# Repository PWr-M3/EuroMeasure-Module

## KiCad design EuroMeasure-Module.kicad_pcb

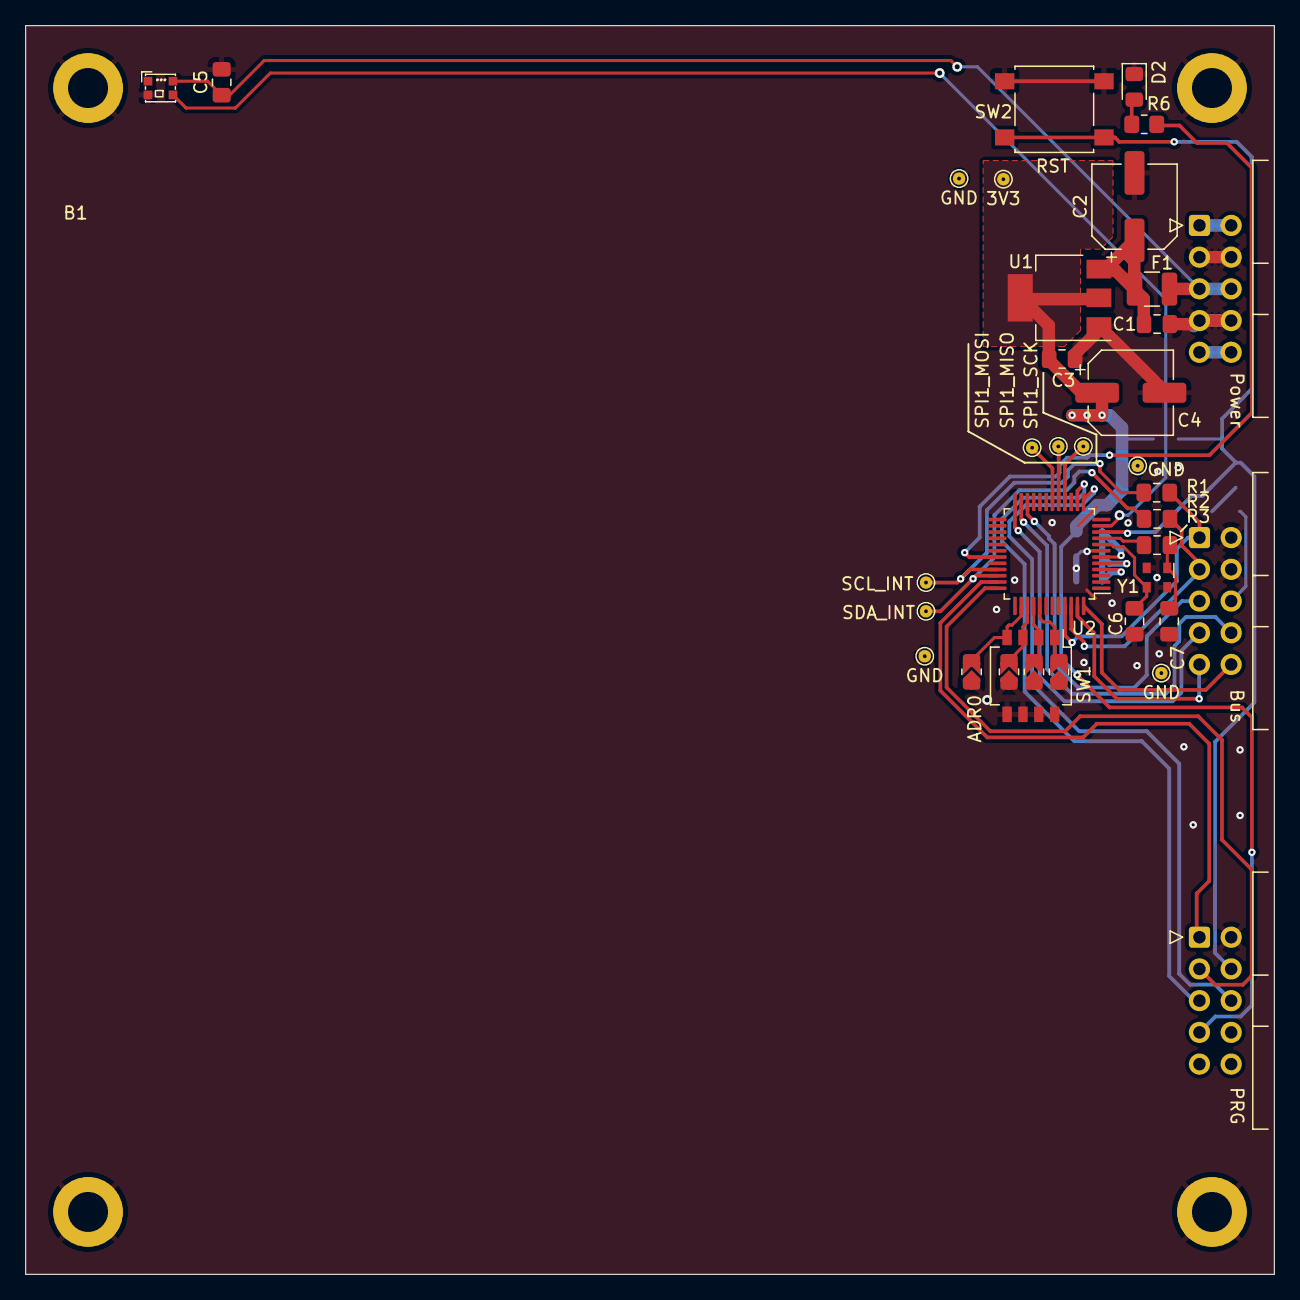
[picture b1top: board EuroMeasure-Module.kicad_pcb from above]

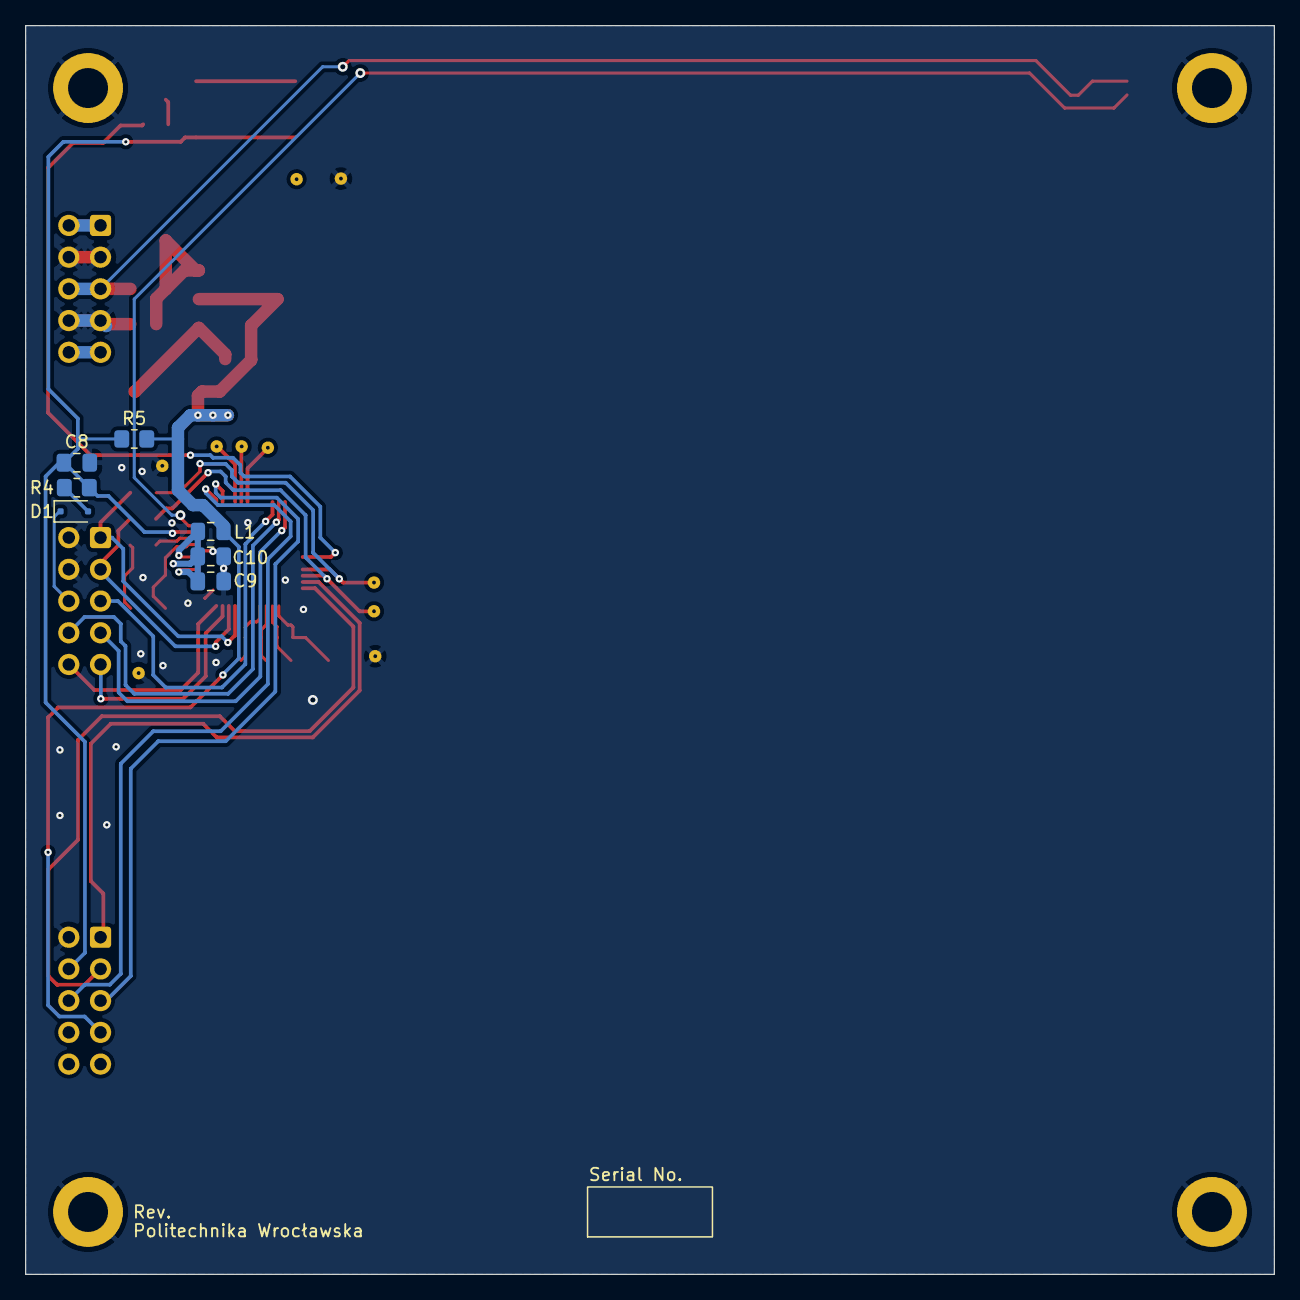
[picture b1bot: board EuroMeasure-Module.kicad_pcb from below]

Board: 2 copper layers, 100.0 x 100.0 mm, 40 parts (7 on the bottom side), 36 nets.

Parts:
B1: EuroBoard; EuroMeasureLED
C1, C3, C5, C10: 10u; C_0805_2012Metric_Pad1.18x1.45mm_HandSolder
C2, C4: 220u; CP_Elec_6.3x7.7
C6, C7: 8p; C_0805_2012Metric_Pad1.18x1.45mm_HandSolder
C8, C9: 100n; C_0805_2012Metric_Pad1.18x1.45mm_HandSolder
D1: 1N4148; D_SOD-323F
D2: RED; LED_0805_2012Metric_Pad1.15x1.40mm_HandSolder
F1: Polyfuse 0.5A; Fuse_1210_3225Metric
JP1: ADR0; R_0805_2012Metric_Jumper
JP2: ADR1; R_0805_2012Metric_Jumper
JP3: ADR2; R_0805_2012Metric_Jumper
JP4: ADR3; R_0805_2012Metric_Jumper
L1: Ferrite; L_0805_2012Metric_Pad1.15x1.40mm_HandSolder
R1, R2, R3: 0R; C_0805_2012Metric_Pad1.18x1.45mm_HandSolder
R4, R5, R6: 1k; R_0805_2012Metric_Pad1.20x1.40mm_HandSolder
SW1: SW_DIP_x04; SW_DIP_SPSTx04_Slide_Omron_A6H-4101_W6.15mm_P1.27mm
SW2: RST; SW_SPST_B3S-1000
TP1: SPI1_SCK; TestPoint_Pad_D1.0mm
TP2: SPI1_MISO; TestPoint_Pad_D1.0mm
TP3: SPI1_MOSI; TestPoint_Pad_D1.0mm
TP4: SCL_INT; TestPoint_Pad_D1.0mm
TP5: SDA_INT; TestPoint_Pad_D1.0mm
TP6, TP7, TP8, TP9: GND; TestPoint_Pad_D1.0mm
TP10: 3V3; TestPoint_Pad_D1.0mm
U1: AZ1117-3V3; SOT-223-3_TabPin2
U2: STM32G030CxT; LQFP-48_7x7mm_P0.5mm
Y1: 16MHz; Oscillator_SMD_Abracon_ASDMB-4Pin_2.5x2.0mm

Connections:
5V_INPUT: B1.5 (5V), B1.6 (5V), B1.D4 (VCC), C5.1, F1.1
15V_INPUT: B1.9 (15V), B1.10 (15V)
+3.3V: B1.27 (3.3V), C3.1, C4.1, L1.1, R5.2, TP10.1, U1.2 (VO)
-15V_INPUT: B1.1 (-15V), B1.2 (-15V)
/EuroMeasure/ADR0: JP1.1, SW1.4, U2.38 (PD0)
/EuroMeasure/ADR1: JP2.1, SW1.3, U2.39 (PD1)
/EuroMeasure/ADR2: JP3.1, SW1.2, U2.40 (PD2)
/EuroMeasure/ADR3: JP4.1, SW1.1, U2.41 (PD3)
/EuroMeasure/GP0: B1.17 (GP0), U2.24 (PB12)
/EuroMeasure/GP1: B1.18 (GP1), U2.23 (PB11)
/EuroMeasure/LED: R6.2, U2.31 (PC7)
/EuroMeasure/MCU_PWR: C9.1, C10.1, L1.2, U2.4 (VBAT), U2.5 (VREF+), U2.6 (VDD/VDDA)
/EuroMeasure/OSC_IN: R3.2, U2.9 (PF1-OSC_OUT)
/EuroMeasure/OSC_OUT: C6.1, U2.8 (PF0-OSC_IN), Y1.3
/EuroMeasure/RDY: B1.20 (RDY), U2.48 (PB9)
/EuroMeasure/RGB_LED: B1.D3 (DI), U2.11 (PA0)
/EuroMeasure/RST: B1.16 (RST), D1.1 (K)
/EuroMeasure/RST_LOCAL: B1.24 (RST), C8.1, R4.1, R5.1, SW2.2, U2.10 (NRST)
/EuroMeasure/RX_DEBUG: B1.25 (RX), U2.14 (PA3)
/EuroMeasure/SCL_EXT: B1.11 (SCL), R1.1, U2.45 (PB6)
/EuroMeasure/SCL_INT: R1.2, TP4.1, U2.33 (PA11)
/EuroMeasure/SDA_EXT: B1.13 (SDA), R2.2, U2.46 (PB7)
/EuroMeasure/SDA_INT: R2.1, TP5.1, U2.34 (PA12)
/EuroMeasure/SPI1_MISO: TP2.1, U2.17 (PA6)
/EuroMeasure/SPI1_MOSI: TP3.1, U2.18 (PA7)
/EuroMeasure/SPI1_SCK: TP1.1, U2.16 (PA5)
/EuroMeasure/SWCLK: B1.23 (SWCLK), U2.36 (PA14)
/EuroMeasure/SWDIO: B1.21 (SWDIO), U2.35 (PA13)
/EuroMeasure/TRG: B1.19 (TRG), U2.47 (PB8)
/EuroMeasure/TX_DEBUG: B1.26 (TX), U2.13 (PA2)
/EuroMeasure/~LOCKOUT: B1.15 (~LOCKOUT), U2.22 (PB10)
GND: B1.3 (GND), B1.4 (GND), B1.7 (GND), B1.8 (GND), B1.12 (GND), B1.14 (GND), B1.22 (GND), B1.D2 (GND), C1.2, C2.2, C3.2, C4.2, C5.2, C6.2, C7.2, C8.2, C9.2, C10.2, D2.1 (K), JP1.2, JP2.2, JP3.2, JP4.2, SW1.5, SW1.6, SW1.7, SW1.8, SW2.1, TP6.1, TP7.1, TP8.1, TP9.1, U1.1 (GND), U2.7 (VSS/VSSA), Y1.2, Y1.4
unnamed: C7.1, R3.1, Y1.1
unnamed: D1.2 (A), R4.2
unnamed: D2.2 (A), R6.1
unnamed: C1.1, C2.1, F1.2, U1.3 (VI)

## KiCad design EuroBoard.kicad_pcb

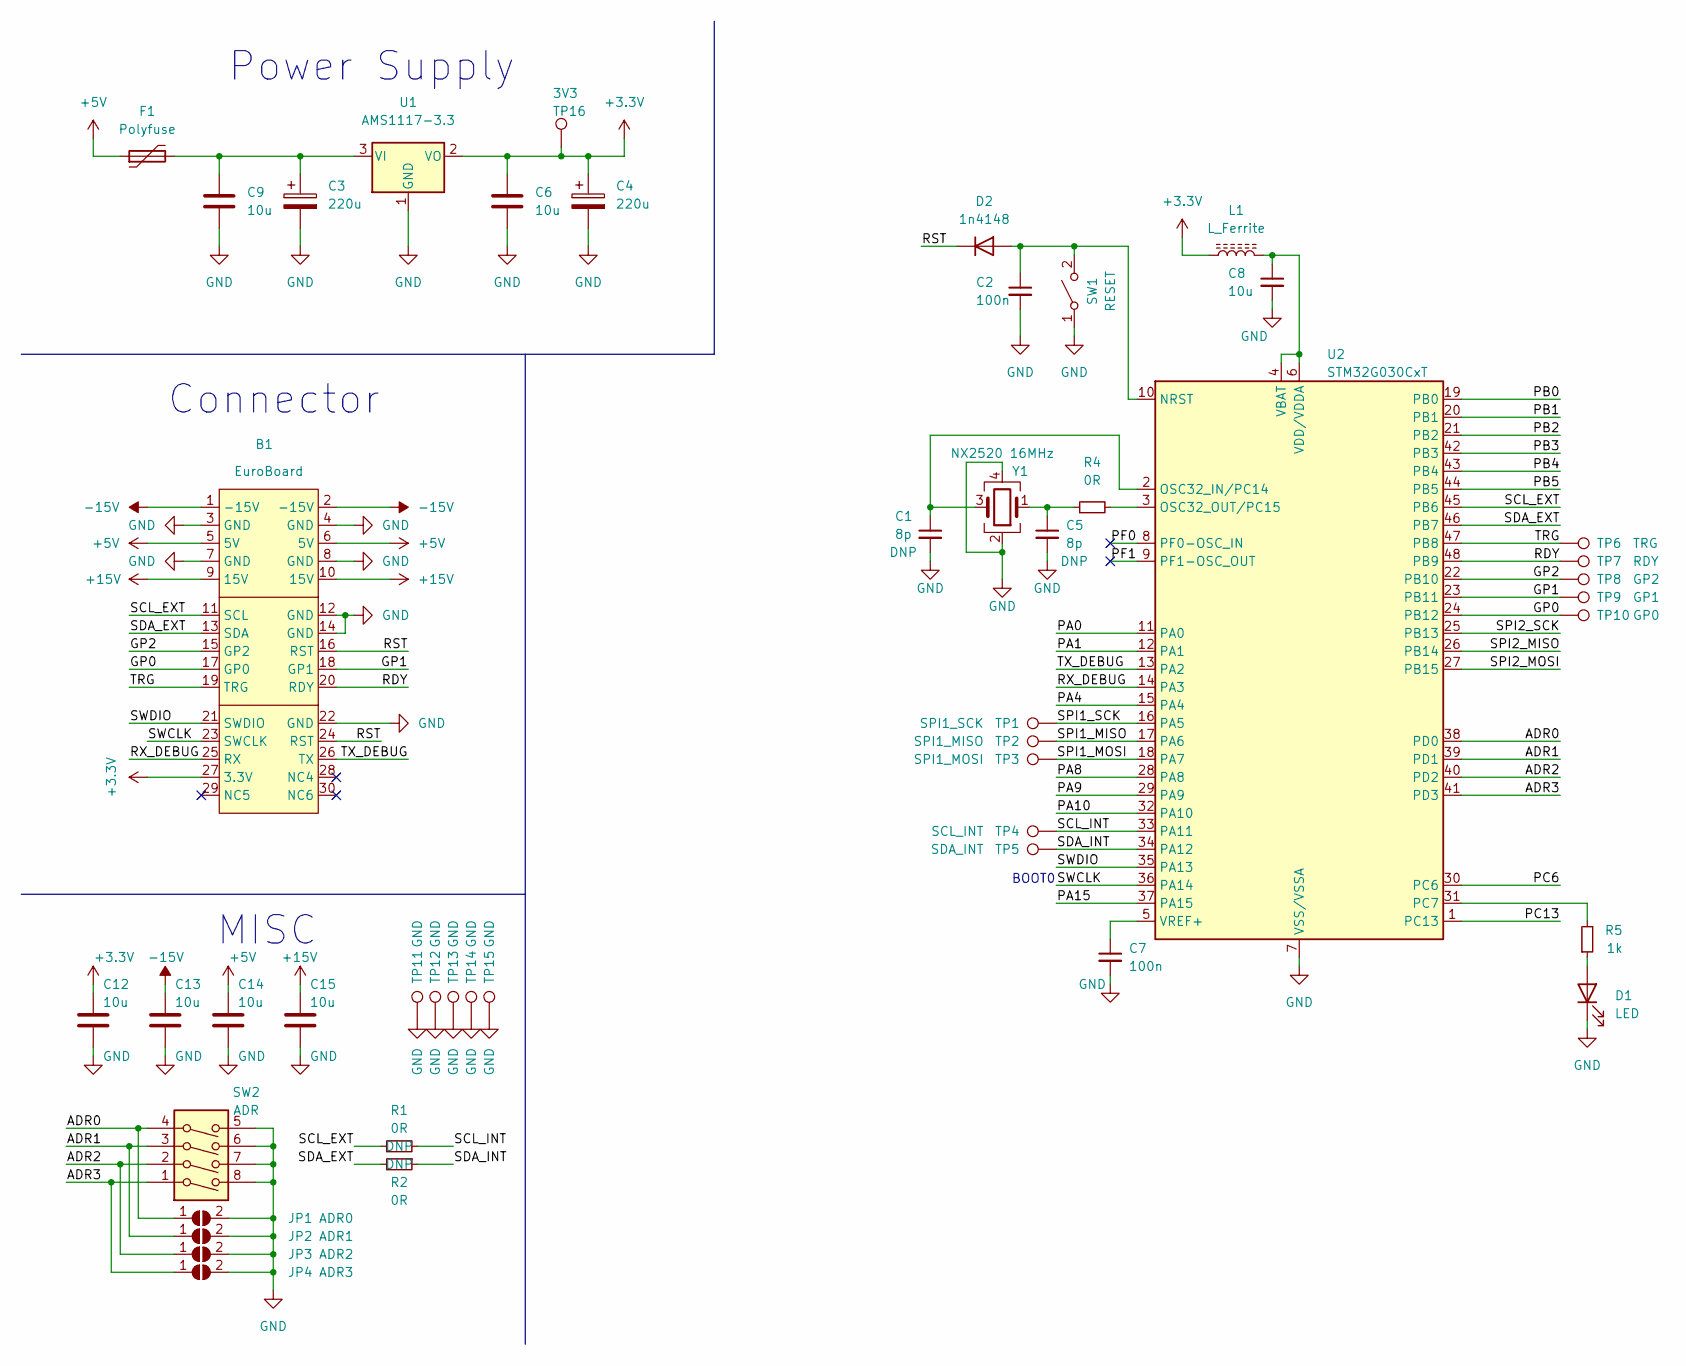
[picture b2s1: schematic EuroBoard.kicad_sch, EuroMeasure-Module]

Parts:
B1: EuroBoard; EuroMeasure
C1, C5: 8p; C_0805_2012Metric_Pad1.18x1.45mm_HandSolder
C2, C7: 100n; C_0805_2012Metric_Pad1.18x1.45mm_HandSolder
C3, C4: 220u; CP_Elec_6.3x7.7
C6, C8, C9, C12, C13, C14, C15: 10u; C_0805_2012Metric_Pad1.18x1.45mm_HandSolder
D1: LED; LED_0805_2012Metric_Pad1.15x1.40mm_HandSolder
D2: 1n4148; D_SOD-123
F1: Polyfuse; Fuse_1210_3225Metric
JP1: ADR0; R_0805_2012Metric_Jumper
JP2: ADR1; R_0805_2012Metric_Jumper
JP3: ADR2; R_0805_2012Metric_Jumper
JP4: ADR3; R_0805_2012Metric_Jumper
L1: L_Ferrite; L_0805_2012Metric_Pad1.15x1.40mm_HandSolder
R1, R2, R4: 0R; C_0805_2012Metric_Pad1.18x1.45mm_HandSolder
R5: 1k; R_0805_2012Metric_Pad1.20x1.40mm_HandSolder
SW1: RESET; SW_SPST_B3S-1000
SW2: ADR; SW_DIP_SPSTx04_Slide_Omron_A6H-4101_W6.15mm_P1.27mm
TP1: SPI1_SCK; TestPoint_Pad_D1.0mm
TP2: SPI1_MISO; TestPoint_Pad_D1.0mm
TP3: SPI1_MOSI; TestPoint_Pad_D1.0mm
TP4: SCL_INT; TestPoint_Pad_D1.0mm
TP5: SDA_INT; TestPoint_Pad_D1.0mm
TP6: TRG; TestPoint_Pad_D1.0mm
TP7: RDY; TestPoint_Pad_D1.0mm
TP8: GP2; TestPoint_Pad_D1.0mm
TP9: GP1; TestPoint_Pad_D1.0mm
TP10: GP0; TestPoint_Pad_D1.0mm
TP11, TP12, TP13, TP14, TP15: GND; TestPoint_Pad_D1.0mm
TP16: 3V3; TestPoint_Pad_D1.0mm
U1: AMS1117-3.3; SOT-223-3_TabPin2
U2: STM32G030CxT; LQFP-48_7x7mm_P0.5mm
Y1: NX2520 16MHz; Oscillator_SMD_Abracon_ASDMB-4Pin_2.5x2.0mm

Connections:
+3.3V: B1.27 (3.3V), C4.1, C6.1, C12.1, L1.1, TP16.1, U1.2 (VO)
+5V: B1.5 (5V), B1.6 (5V), C14.1, F1.1
+15V: B1.9 (15V), B1.10 (15V), C15.1
-15V: B1.1 (-15V), B1.2 (-15V), C13.1
/ADR0: JP1.1 (A), SW2.4, U2.38 (PD0)
/ADR1: JP2.1 (A), SW2.3, U2.39 (PD1)
/ADR2: JP3.1 (A), SW2.2, U2.40 (PD2)
/ADR3: JP4.1 (A), SW2.1, U2.41 (PD3)
/GP0: B1.17 (GP0), TP10.1, U2.24 (PB12)
/GP1: B1.18 (GP1), TP9.1, U2.23 (PB11)
/GP2: B1.15 (GP2), TP8.1, U2.22 (PB10)
/PA0: U2.11 (PA0)
/PA1: U2.12 (PA1)
/PA4: U2.15 (PA4)
/PA8: U2.28 (PA8)
/PA9: U2.29 (PA9)
/PA10: U2.32 (PA10)
/PA15: U2.37 (PA15)
/PB0: U2.19 (PB0)
/PB1: U2.20 (PB1)
/PB2: U2.21 (PB2)
/PB3: U2.42 (PB3)
/PB4: U2.43 (PB4)
/PB5: U2.44 (PB5)
/PC6: U2.30 (PC6)
/PC13: U2.1 (PC13)
/PF0: U2.8 (PF0-OSC_IN)
/PF1: U2.9 (PF1-OSC_OUT)
/RDY: B1.20 (RDY), TP7.1, U2.48 (PB9)
/RST: B1.16 (RST), B1.24 (RST), D2.1 (K)
/RX_DEBUG: B1.25 (RX), U2.14 (PA3)
/SCL_EXT: B1.11 (SCL), R1.1, U2.45 (PB6)
/SCL_INT: R1.2, TP4.1, U2.33 (PA11)
/SDA_EXT: B1.13 (SDA), R2.2, U2.46 (PB7)
/SDA_INT: R2.1, TP5.1, U2.34 (PA12)
/SPI1_MISO: TP2.1, U2.17 (PA6)
/SPI1_MOSI: TP3.1, U2.18 (PA7)
/SPI1_SCK: TP1.1, U2.16 (PA5)
/SPI2_MISO: U2.26 (PB14)
/SPI2_MOSI: U2.27 (PB15)
/SPI2_SCK: U2.25 (PB13)
/SWCLK: B1.23 (SWCLK), U2.36 (PA14)
/SWDIO: B1.21 (SWDIO), U2.35 (PA13)
/TRG: B1.19 (TRG), TP6.1, U2.47 (PB8)
/TX_DEBUG: B1.26 (TX), U2.13 (PA2)
GND: B1.3 (GND), B1.4 (GND), B1.7 (GND), B1.8 (GND), B1.12 (GND), B1.14 (GND), B1.22 (GND), C1.2, C2.2, C3.2, C4.2, C5.2, C6.2, C7.2, C8.2, C9.2, C12.2, C13.2, C14.2, C15.2, D1.1 (K), JP1.2 (B), JP2.2 (B), JP3.2 (B), JP4.2 (B), SW1.1 (A), SW2.5, SW2.6, SW2.7, SW2.8, TP11.1, TP12.1, TP13.1, TP14.1, TP15.1, U1.1 (GND), U2.7 (VSS/VSSA), Y1.2, Y1.4
unnamed: C1.1, U2.2 (OSC32_IN/PC14), Y1.3
unnamed: C2.1, D2.2 (A), SW1.2 (B), U2.10 (NRST)
unnamed: C3.1, C9.1, F1.2, U1.3 (VI)
unnamed: C5.1, R4.1, Y1.1
unnamed: C7.1, U2.5 (VREF+)
unnamed: C8.1, L1.2, U2.4 (VBAT), U2.6 (VDD/VDDA)
unnamed: D1.2 (A), R5.1
unnamed: R4.2, U2.3 (OSC32_OUT/PC15)
unnamed: R5.2, U2.31 (PC7)

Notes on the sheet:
Connector
BOOT0
MISC
Power Supply

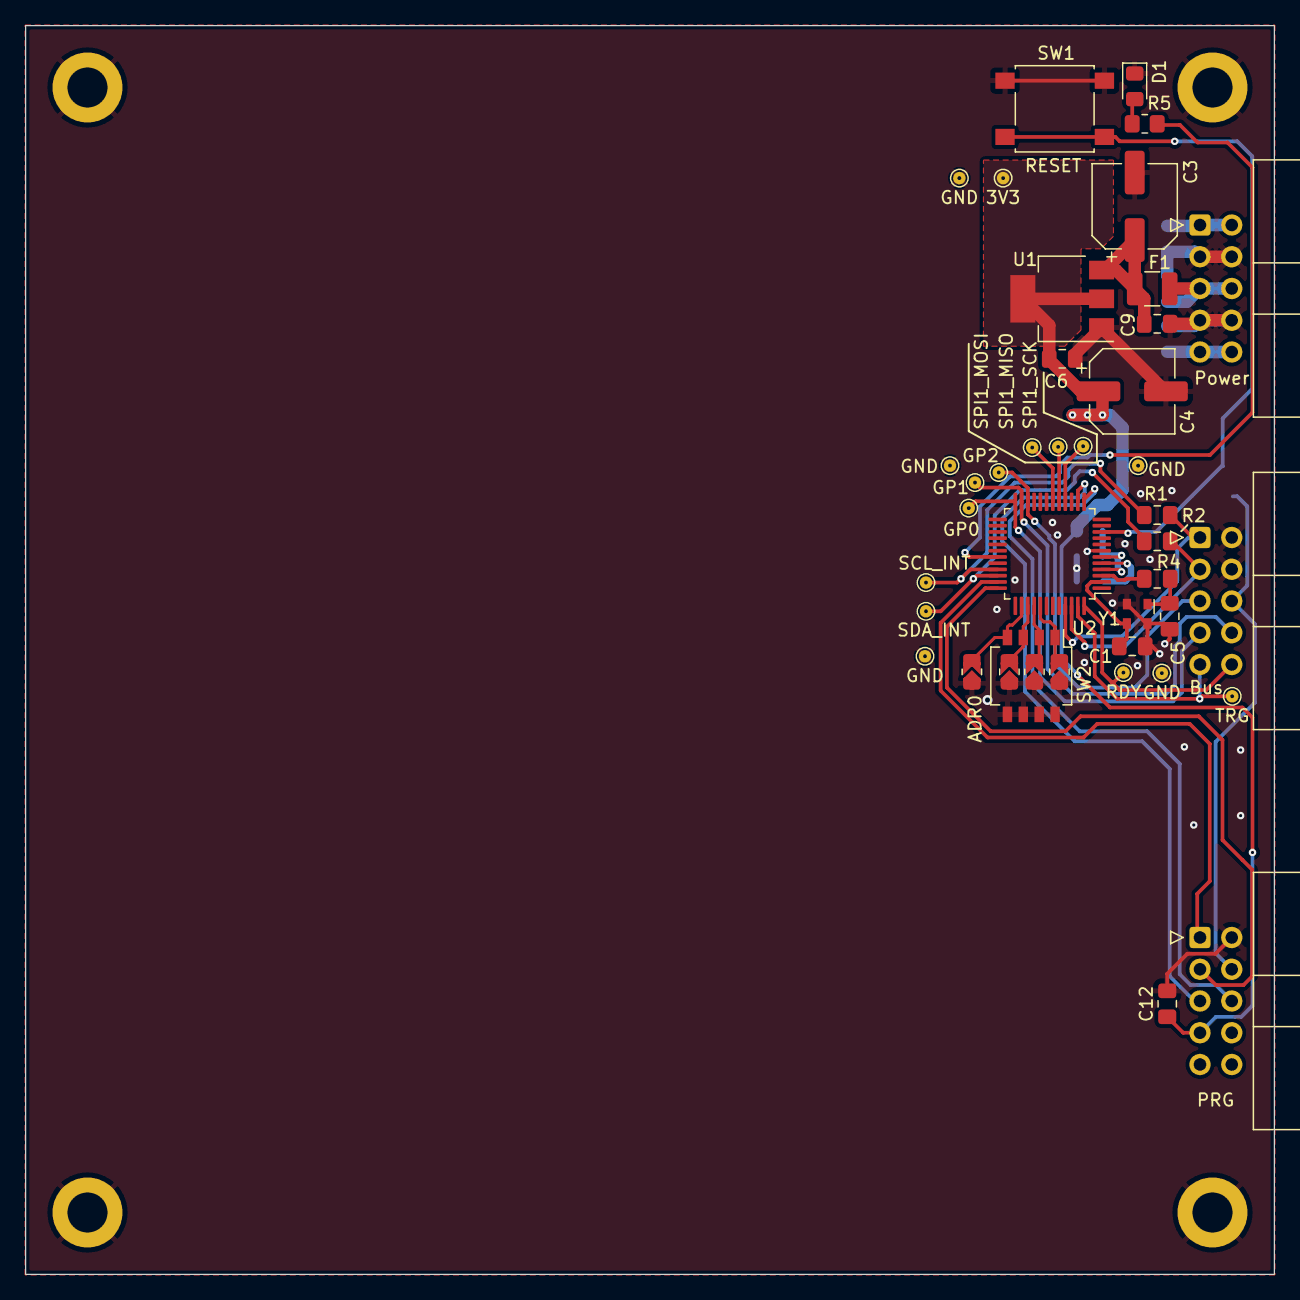
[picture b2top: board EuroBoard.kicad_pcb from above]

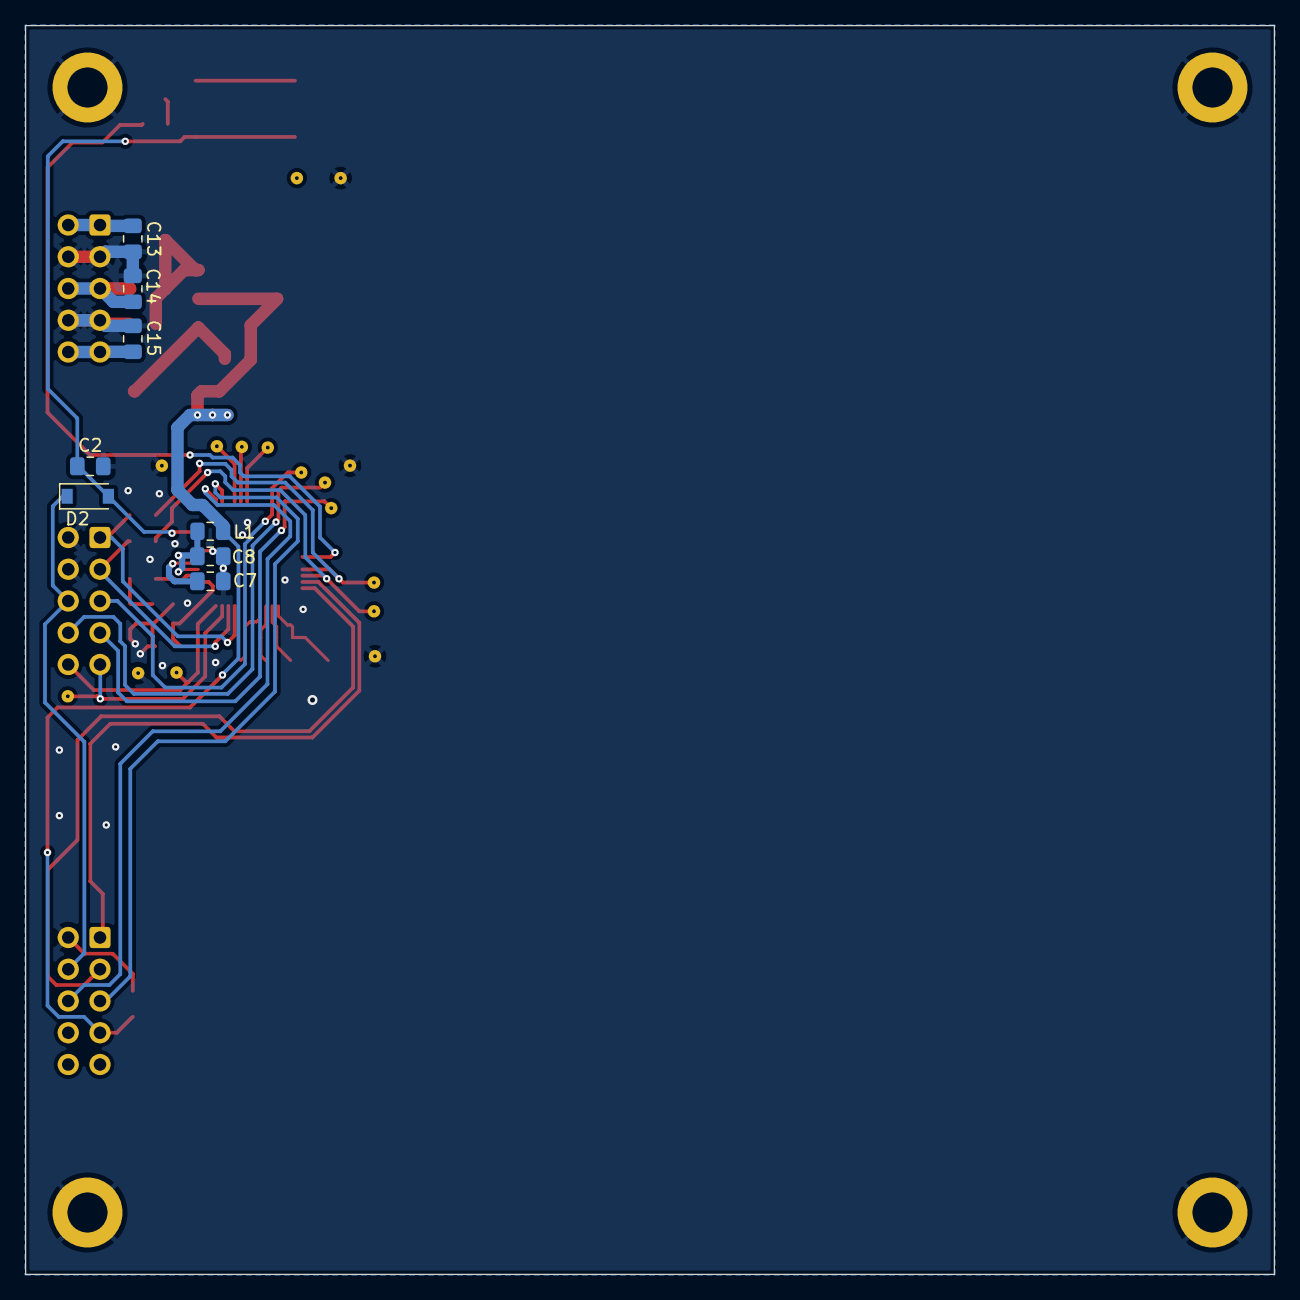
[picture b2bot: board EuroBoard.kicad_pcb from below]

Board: 2 copper layers, 99.9 x 99.9 mm, 47 parts (8 on the bottom side), 35 nets.

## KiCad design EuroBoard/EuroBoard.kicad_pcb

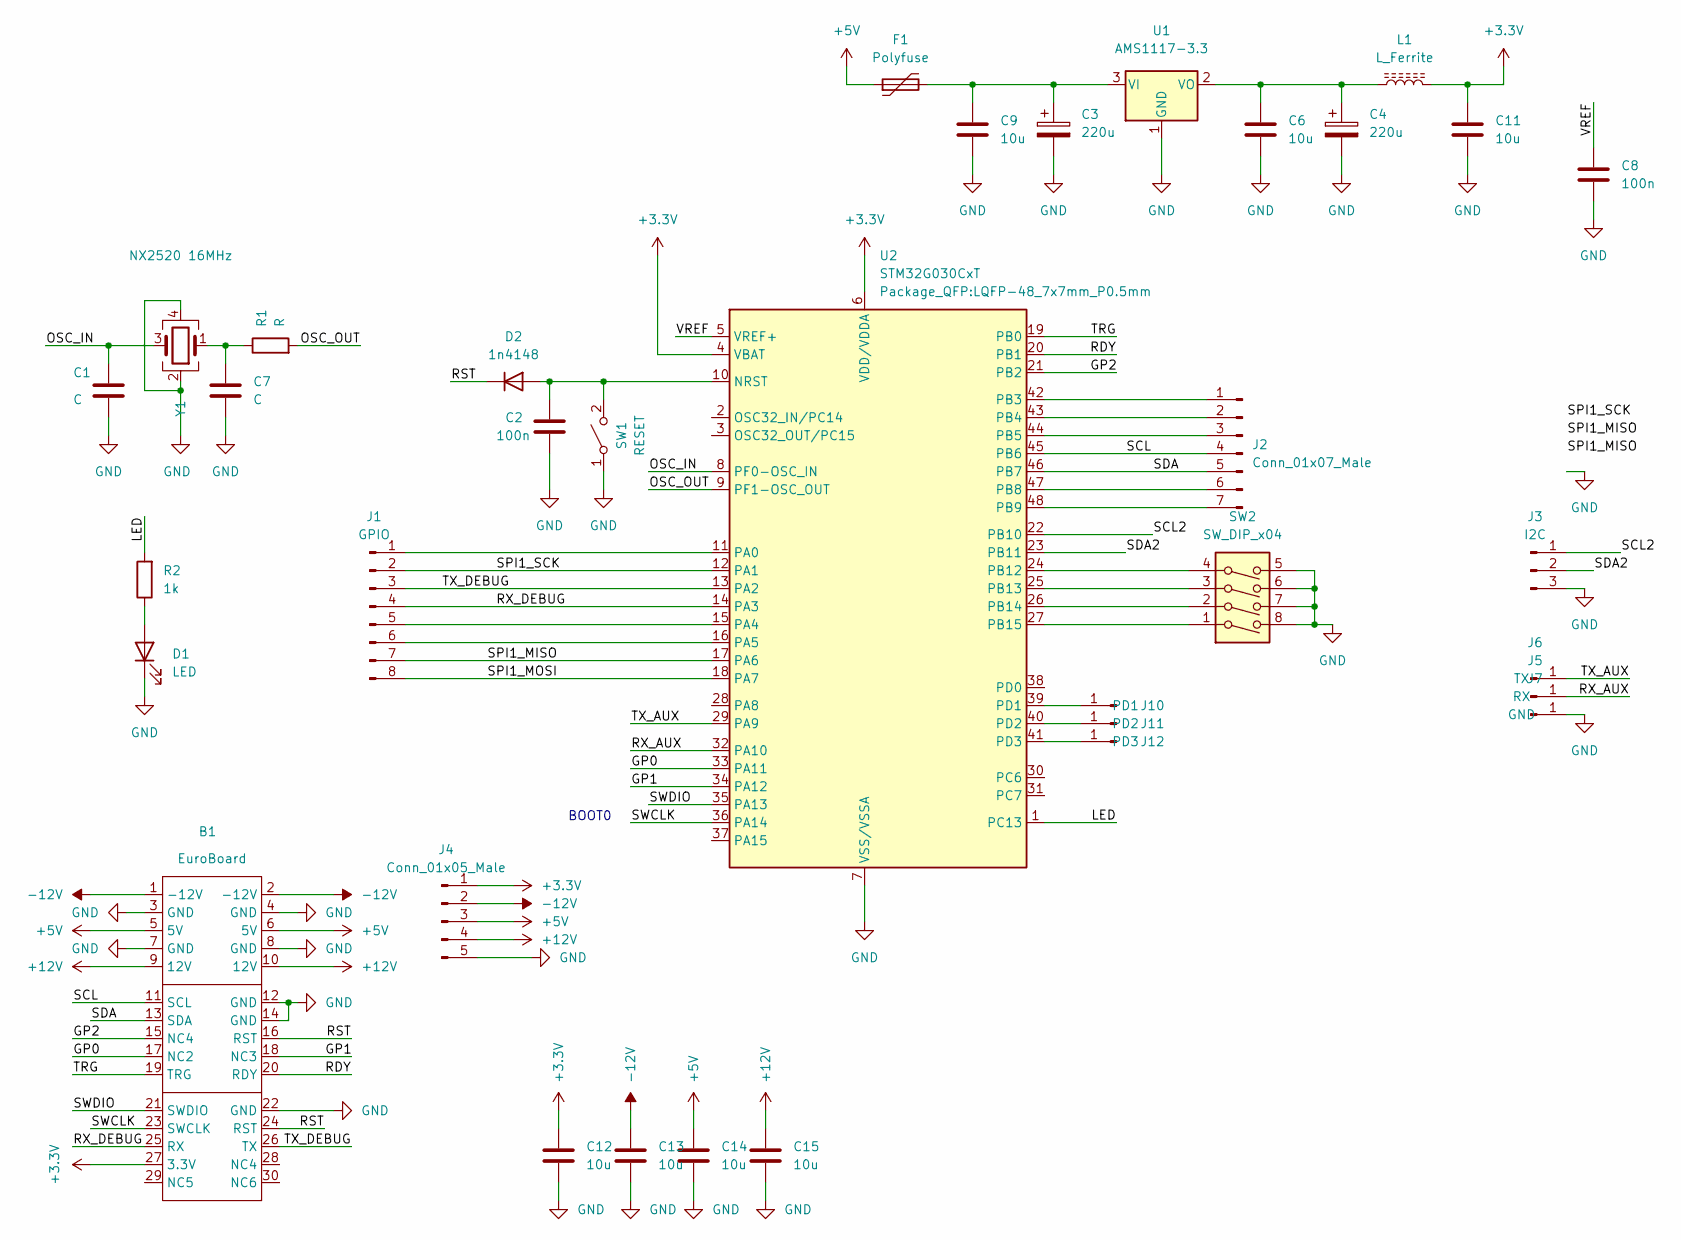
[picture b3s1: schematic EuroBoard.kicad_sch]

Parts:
B1: EuroBoard; EuroMeasure
C1, C7: C; C_0805_2012Metric_Pad1.18x1.45mm_HandSolder
C2, C8: 100n; C_0805_2012Metric_Pad1.18x1.45mm_HandSolder
C3, C4: 220u; CP_Elec_6.3x7.7
C6, C9, C11, C12, C13, C14, C15: 10u; C_0805_2012Metric_Pad1.18x1.45mm_HandSolder
D1: LED; LED_0805_2012Metric_Pad1.15x1.40mm_HandSolder
D2: 1n4148; D_SOD-123
F1: Polyfuse; Fuse_1210_3225Metric
J1: GPIO; PinHeader_1x08_P2.54mm_Vertical
J2: Conn_01x07_Male; PinHeader_1x07_P2.54mm_Vertical
J3: I2C; PinHeader_1x03_P2.54mm_Vertical
J4: Conn_01x05_Male; PinHeader_1x05_P2.54mm_Vertical
J5: RX; TestPoint_Pad_1.0x1.0mm
J6: TX; TestPoint_Pad_1.0x1.0mm
J7: GND; TestPoint_Pad_1.0x1.0mm
J10: PD1; TestPoint_Pad_1.0x1.0mm
J11: PD2; TestPoint_Pad_1.0x1.0mm
J12: PD3; TestPoint_Pad_1.0x1.0mm
L1: L_Ferrite; L_0805_2012Metric_Pad1.15x1.40mm_HandSolder
R1: R; R_0805_2012Metric_Pad1.20x1.40mm_HandSolder
R2: 1k; R_0805_2012Metric_Pad1.20x1.40mm_HandSolder
SW1: RESET; SW_SPST_B3S-1000
SW2: SW_DIP_x04; SW_DIP_SPSTx04_Slide_Omron_A6H-4101_W6.15mm_P1.27mm
U1: AMS1117-3.3; SOT-223-3_TabPin2
U2: STM32G030CxT; LQFP-48_7x7mm_P0.5mm
Y1: NX2520 16MHz; Oscillator_SMD_Abracon_ASDMB-4Pin_2.5x2.0mm

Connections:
+3.3V: B1.27 (3.3V), C11.1, C12.1, J4.1, L1.2, U2.4 (VBAT), U2.6 (VDD/VDDA)
+5V: B1.5 (5V), B1.6 (5V), C14.1, F1.1, J4.3
+12V: B1.9 (12V), B1.10 (12V), C15.1, J4.4
-12V: B1.1 (-12V), B1.2 (-12V), C13.1, J4.2
/GP0: B1.17 (NC2), U2.33 (PA11)
/GP1: B1.18 (NC3), U2.34 (PA12)
/GP2: B1.15 (NC4), U2.21 (PB2)
/LED: R2.2, U2.1 (PC13)
/OSC_IN: C1.1, U2.8 (PF0-OSC_IN), Y1.3
/OSC_OUT: R1.2, U2.9 (PF1-OSC_OUT)
/RDY: B1.20 (RDY), U2.20 (PB1)
/RST: B1.16 (RST), B1.24 (RST), D2.1 (K)
/RX_AUX: J5.1, U2.32 (PA10)
/RX_DEBUG: B1.25 (RX), J1.4, U2.14 (PA3)
/SCL: B1.11 (SCL), J2.4, U2.45 (PB6)
/SCL2: J3.1, U2.22 (PB10)
/SDA: B1.13 (SDA), J2.5, U2.46 (PB7)
/SDA2: J3.2, U2.23 (PB11)
/SPI1_MISO: J1.7, U2.17 (PA6)
/SPI1_MOSI: J1.8, U2.18 (PA7)
/SPI1_SCK: J1.2, U2.12 (PA1)
/SWCLK: B1.23 (SWCLK), U2.36 (PA14)
/SWDIO: B1.21 (SWDIO), U2.35 (PA13)
/TRG: B1.19 (TRG), U2.19 (PB0)
/TX_AUX: J6.1, U2.29 (PA9)
/TX_DEBUG: B1.26 (TX), J1.3, U2.13 (PA2)
/VREF: C8.1, U2.5 (VREF+)
GND: B1.3 (GND), B1.4 (GND), B1.7 (GND), B1.8 (GND), B1.12 (GND), B1.14 (GND), B1.22 (GND), C1.2, C2.2, C3.2, C4.2, C6.2, C7.2, C8.2, C9.2, C11.2, C12.2, C13.2, C14.2, C15.2, D1.1 (K), J3.3, J4.5, J7.1, SW1.1 (A), SW2.5, SW2.6, SW2.7, SW2.8, U1.1 (GND), U2.7 (VSS/VSSA), Y1.2, Y1.4
unnamed: C2.1, D2.2 (A), SW1.2 (B), U2.10 (NRST)
unnamed: C3.1, C9.1, F1.2, U1.3 (VI)
unnamed: C4.1, C6.1, L1.1, U1.2 (VO)
unnamed: C7.1, R1.1, Y1.1
unnamed: D1.2 (A), R2.1
unnamed: J1.1, U2.11 (PA0)
unnamed: J1.5, U2.15 (PA4)
unnamed: J1.6, U2.16 (PA5)
unnamed: J2.1, U2.42 (PB3)
unnamed: J2.2, U2.43 (PB4)
unnamed: J2.3, U2.44 (PB5)
unnamed: J2.6, U2.47 (PB8)
unnamed: J2.7, U2.48 (PB9)
unnamed: J11.1, U2.40 (PD2)
unnamed: J12.1, U2.41 (PD3)
unnamed: SW2.1, U2.27 (PB15)
unnamed: SW2.2, U2.26 (PB14)
unnamed: SW2.3, U2.25 (PB13)
unnamed: SW2.4, U2.24 (PB12)
unnamed: J10.1, U2.39 (PD1)

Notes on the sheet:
BOOT0

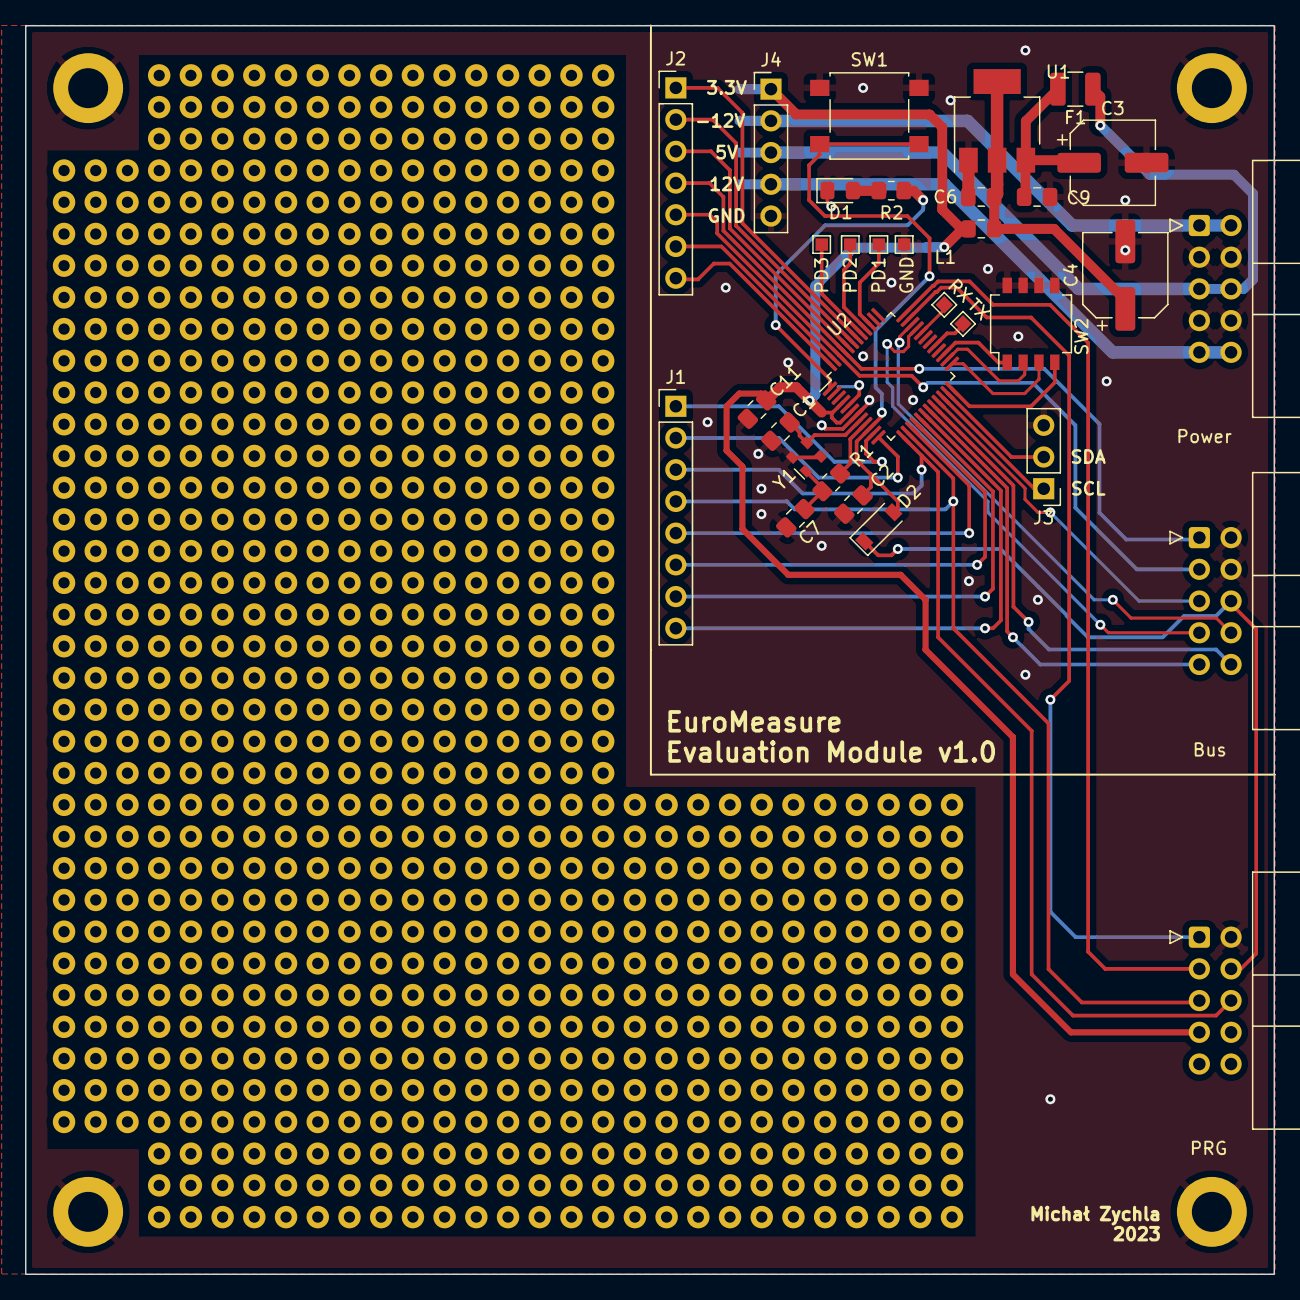
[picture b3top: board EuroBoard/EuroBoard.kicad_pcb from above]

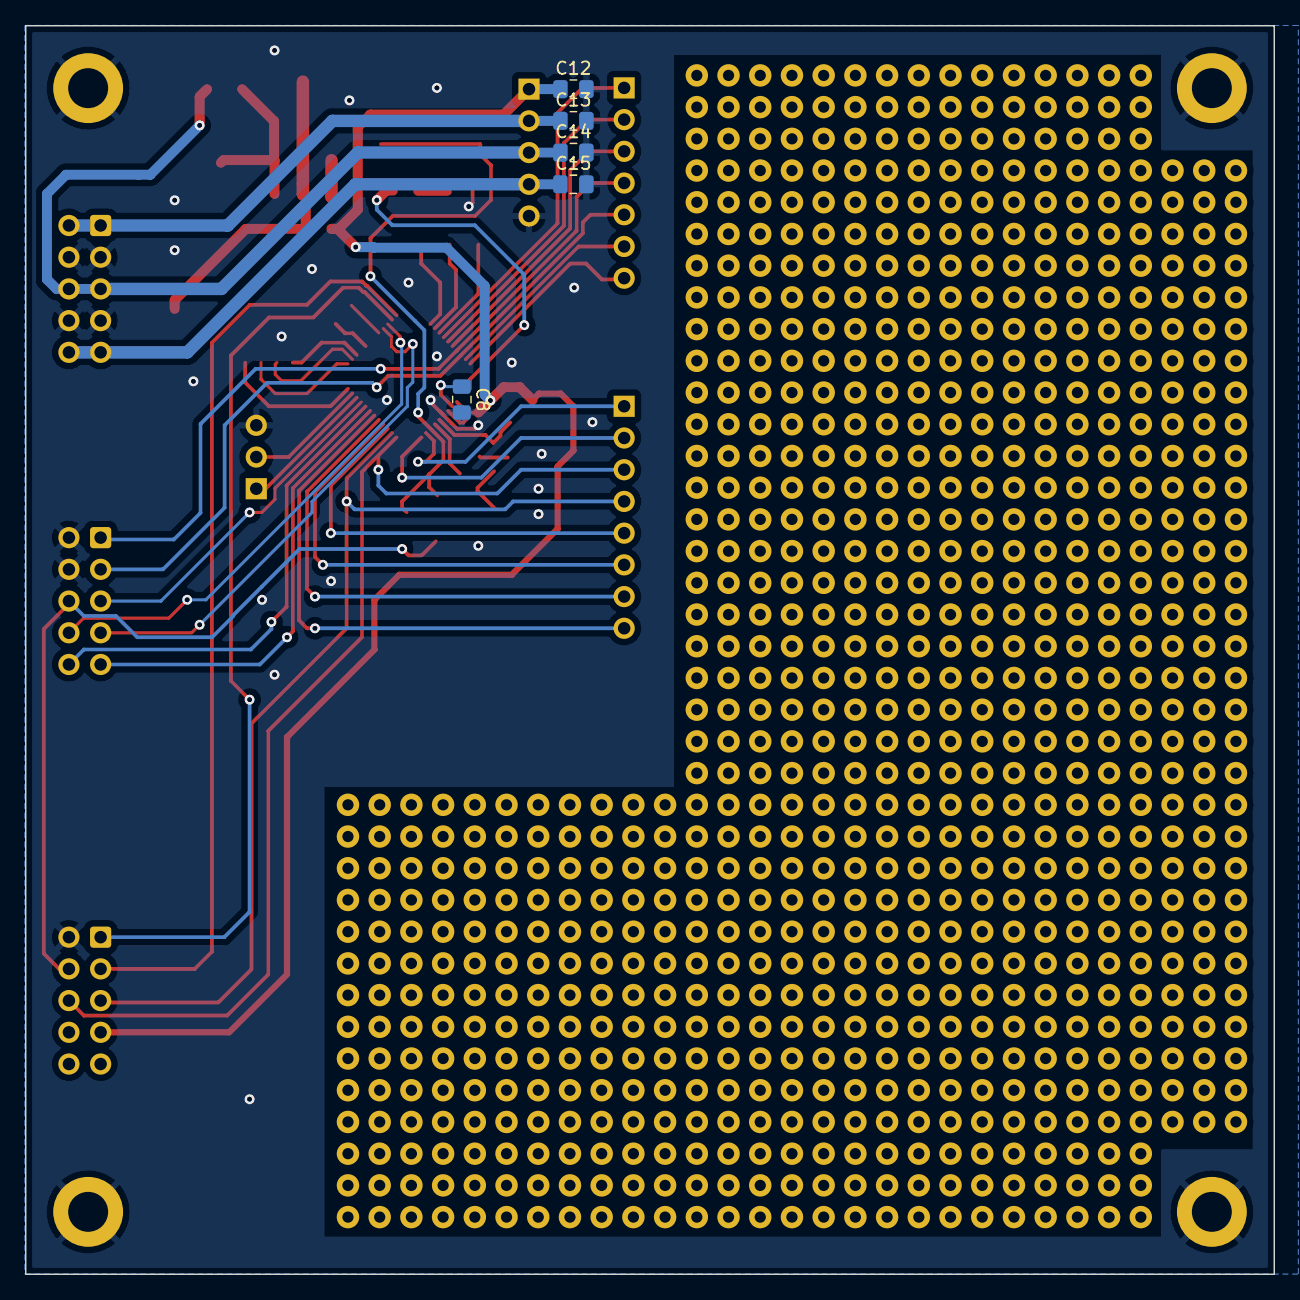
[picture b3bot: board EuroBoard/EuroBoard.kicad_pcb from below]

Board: 2 copper layers, 100.0 x 100.0 mm, 35 parts (5 on the bottom side), 48 nets.

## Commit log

2023-01-22 MCU and 3.3V source
2023-01-22 EuroBoard connector added
2023-01-22 mend
2023-01-22 Almost done
2023-01-22 Started doing PCB
2023-01-23 Board outline
2023-01-23 Board awaiting review
2023-01-23 Removed unnecessary caps
2023-01-24 Added alectrolytic capacitors
2023-01-24 Connected free bus lines to GPIO
2023-01-24 DRC check and corrections
2023-01-24 Silkscreen cosmetics
2023-01-24 Generated gerber files
2023-01-27 Reorganized repo
2023-01-27 Rework
2023-01-27 Added jumpers for address selection
2023-02-02 removed R3 from pcb
2023-02-05 Fixed pin numbering error
2023-02-06 Changed bus voltage from 12V to 15V
2023-02-08 Fixed xtal connection
2023-03-06 Fixed programmer reset
2023-03-21 Updated euroboard footprint to accept lockout
2023-04-08 Basic project created
2023-04-16 Added MPN and Mouser MCU
2023-04-16 MPN and MOUSER added PSU
2023-04-16 Symbols changed to Library
2023-04-23 Updated module to current standards
2023-04-23 Updated PCB to current standards
2023-08-21 Converted for use as the single EuroMeasure.sch file
2023-08-22 Revised labelling
2023-08-28 Cleaned up schematic
2023-08-28 Cleaned up PCB
2023-08-30 Revised sheet path
2023-08-30 Reverted duplicated components
2023-08-30 Fixed VREF
2023-09-04 Updated DRC constraints
2023-09-12 Updated gitignore
2023-09-14 Cleaned up repository
2023-10-17 Fixed reset pullup
2023-10-25 Edited visibility in bom
